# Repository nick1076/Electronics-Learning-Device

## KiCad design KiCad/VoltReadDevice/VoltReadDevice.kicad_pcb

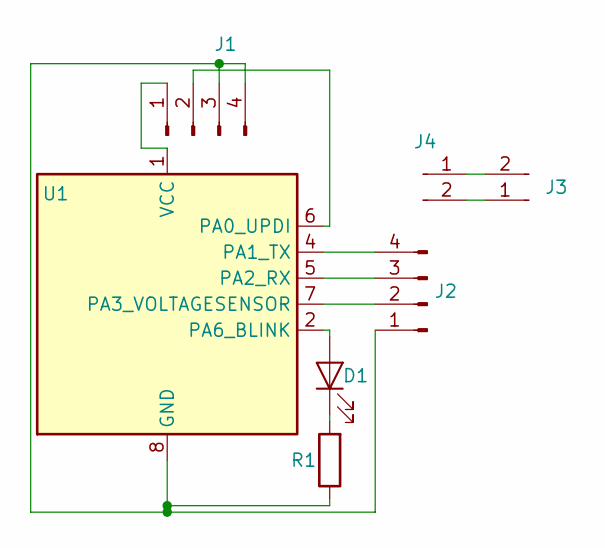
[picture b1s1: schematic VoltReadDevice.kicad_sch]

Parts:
D1: LED; LED_1206
J1, J2: Conn_PinHeader_1x04_P2.54mm_Horizontal_SMD; PinHeader_1x04_P2.54mm_Horizontal_SMD
J3, J4: Conn_PinHeader_1x02_P2.54mm_Horizontal_SMD; PinHeader_UPDI_01x02_P2.54mm_Horizontal_SMD
R1: R; R_1206
U1: ATtiny412-SS; SOIC-8_3.9x4.9mm_P1.27mm

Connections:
unnamed: D1.1 (K), R1.2
unnamed: D1.2 (A), U1.2 (PA6_BLINK)
unnamed: J1.1, U1.1 (VCC)
unnamed: J1.2, U1.6 (PA0_UPDI)
unnamed: J1.3, J1.4, J2.1, R1.1, U1.8 (GND)
unnamed: J2.2, U1.7 (PA3_VOLTAGESENSOR)
unnamed: J2.3, U1.5 (PA2_RX)
unnamed: J2.4, U1.4 (PA1_TX)
unnamed: J3.1, J4.2
unnamed: J3.2, J4.1

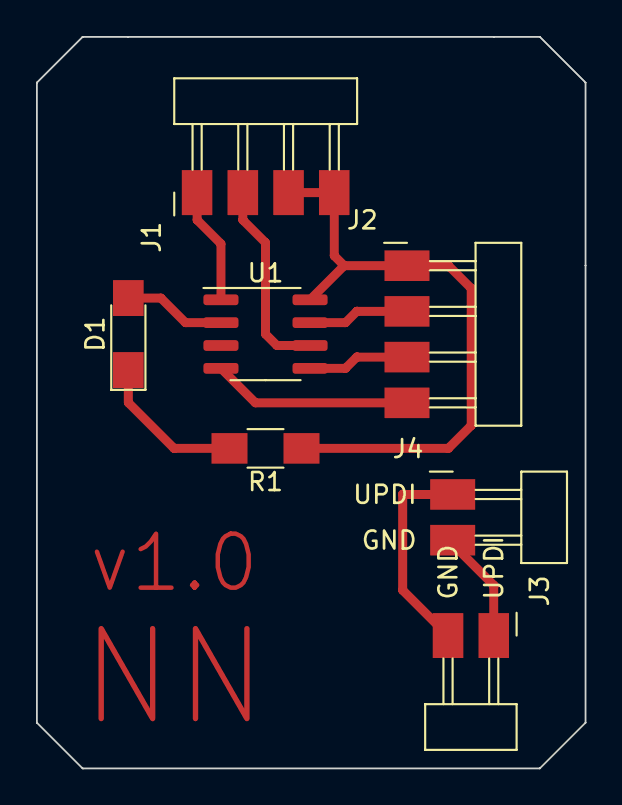
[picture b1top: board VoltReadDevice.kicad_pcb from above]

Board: 2 copper layers, 30.5 x 40.6 mm, 7 parts (0 on the bottom side), 10 nets.

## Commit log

2022-10-10 v1.0 - Initial
2022-10-16 v1.1 - Unity Addition
    Added Unity Assets/Visual Component.
2022-10-30 v1.2 - arduino mods
2022-10-30 v1.3 - Visual Updates
2022-11-12 v1.4 - Voltage Graph & Lag Fix
2022-11-19 v1.5 - Visual Overhaul & Tab/Window System
2022-11-20 v1.6 - Further Fixes & Moving
2022-11-22 v1.7 - Addition of Modes
2022-11-22 v1.8 - Transistor Visual Element
2022-11-27 v1.9 - Lesson System
2022-11-27 v2.0 - Pull Down Resistor Lesson Development
2022-11-27 v2.1 - Missing Scripts Push
2022-11-28 v2.2 - Visual Improvements & Fixes
2022-11-30 v2.3 - Physical Device KiCad Development
2022-12-01 v2.4 - Finished KiCad Design
2022-12-14 v2.5 - Updates
2026-06-07 Push
